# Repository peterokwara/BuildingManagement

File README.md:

# Table of Contents

- [Table of Contents](#table-of-contents)
- [Building Management System](#building-management-system)
- [Video example](#video-example)
- [Dashboard](#dashboard)
- [Hardware setup](#hardware-setup)
  - [Esp & Current sensor](#esp--current-sensor)
  - [Esp & Dht sensor](#esp--dht-sensor)
  - [Esp & Motion sensor](#esp--motion-sensor)
  - [Esp & Relay](#esp--relay)
- [Installation](#installation)
  - [Esp](#esp)
  - [Raspberry Pi](#raspberry-pi)
  - [Server](#server)
  - [Client](#client)
- [Usage](#usage)
  - [Raspberry Pi](#raspberry-pi-1)
  - [Website (server and client)](#website-server-and-client)
- [Contributing](#contributing)
- [License](#license)

# Building Management System

This project seeks to demonstrate the use of MQTT protocol and MERN stack for building an IoT Building Management System for commercial usage, where parameters such as building occupancy, energy demand, andenergy consumption are measured and displayed on an online database and dashboard.

A more detailed description of the project can be found [here](https://github.com/peterokwara/BuildingManagement/blob/master/Project%20Report.pdf).

# Video example

A video of the project working (hardware)

<a href="https://www.youtube.com/watch?v=Yh3uR8R79lM" target="_blank"></a>

A video of the project working (software)

<a href="https://youtu.be/3eJK0t_gp44
" target="_blank"></a>

# Dashboard

You can access the dashboard after you sign up [here](https://thawing-scrubland-94209.herokuapp.com/)

# Hardware setup

## Esp & Current sensor

Circuit design

Board design and the final look

## Esp & Dht sensor

Circuit design

Board design and the final look

## Esp & Motion sensor

Circuit design

Board design and the final look

## Esp & Relay

Circuit design

Board design and the final look

# Installation

## Esp

Installing in an ESP8266-01 and NodeMCU involves pushing the python files into the device whether it's via a usb to ttl or just a usb cable. This can be done using the command

```bash
sudo ampy --port /dev/ttyUSB0 --baud 115200 put main.py
sudo ampy --port /dev/ttyUSB0 --baud 115200 put config.py
sudo ampy --port /dev/ttyUSB0 --baud 115200 put connectWifi.py
```

You need to create a config.py file with the following information for each and every esp folder (current-sensor, dht-sensor, motion-sensor, relay-bulb, relay-fan)

```python
MQTT_CONFIG = {
    'SENSOR_ID': '',
    'MQTT_HOST': '',
    'PORT': '',
    'PUB_TOPIC': ''
}

WIFI_CONFIG = {
    'WIFI_ESSID': '',
    'WIFI_PASSWORD': ''
}
```

## Raspberry Pi

To install npm packages used for the Raspberry Pi, you run.

```bash
npm install axios mongoose mqtt
```

You also need to create a config folder and have two files that contain config/broker.js

```js
module.exports = {
  brokerUrl: ""
};
```

and config/server.js

```js
module.exports = {
  serverUrl: ""
};
```

## Server

To install npm packages used for the server, you run.

```bash
npm install axios bcryptjs body-parser concurrently cors express gravatar jsonwebtoken mongoose mqtt passport passport-jwt recharts validator
```

You also need to have a config/keys_dev.js with the configuration above. The mongoUri and secretOrKey are obtained when you create a mongodb on https://mlab.com the database I used.

```js
module.exports = {
  mongoUri: "",
  secretOrKey: ""
};
```

## Client

To install npm packages used for the client, you run.

```bash
npm install jwt-decode axios react-redux redux recharts redux-thunk semantic-ui-css semantic-ui-react
```

# Usage

## Raspberry Pi

To run the code for Raspberry Pi just cd into the folder and run

```bash
node app.js
```

To ensure that the Raspberry Pi runs the code whenever it boots, edit the rc.local file

```
sudo nano /etc/rc.local
```

and add

```
node app.js &
```

## Website (server and client)

To run a local development of the website, all you need to do is to do the installation setup then once that is done

```
cd site && npm run dev
```

# Contributing

Pull requests are welcome. For major changes, please open an issue first to discuss what you would like to change.

Please make sure to update tests as appropriate.

# License

[MIT](https://github.com/peterokwara/BuildingManagement/blob/master/LICENSE)

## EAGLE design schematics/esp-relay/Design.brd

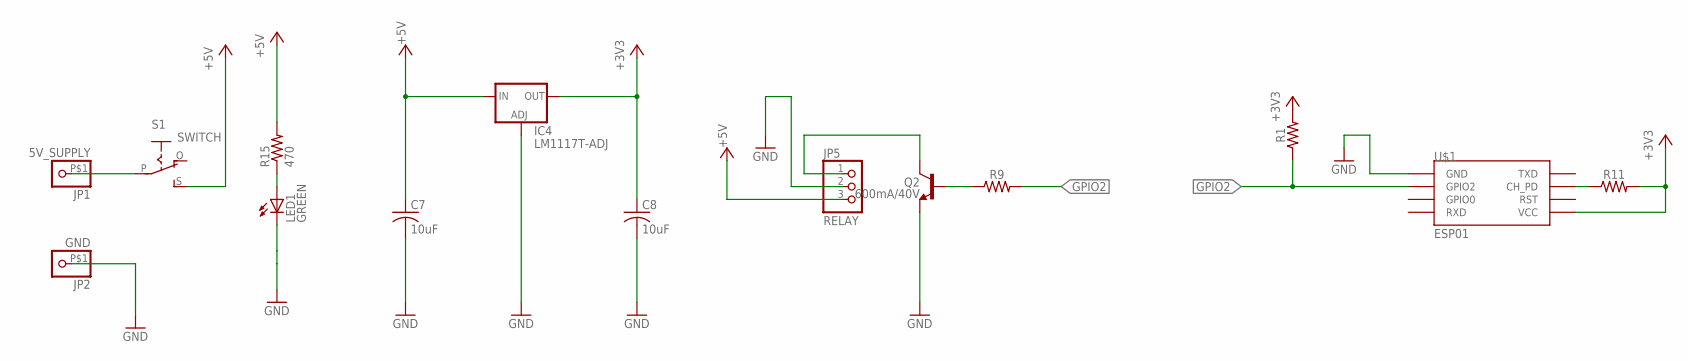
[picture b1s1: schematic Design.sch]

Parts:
C7, C8: 10uF; C025-025X050
IC4: LM1117T-ADJ; TO220
JP1: 5V_SUPPLY; 1X1-BIGPOGO
JP2: GND; 1X1-BIGPOGO
JP5: RELAY; 1X03
LED1: GREEN; LED5MM
Q2: 600mA/40V; TO-92
R1, R11: 10k; 0207/12
R9: 4.7k; 0207/12
R15: 470; 0207/12
S1: SWITCH; EG1218
U$1: ESP01

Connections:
+3V3: C8.1, IC4.2 (OUT), R1.2, R11.2, U$1.VCC
+5V: C7.1, IC4.3 (IN), JP5.3, R15.2, S1.S
GND: C7.2, C8.2, IC4.1 (ADJ), JP2.P$1, JP5.2, LED1.K (C), Q2.3 (E), U$1.GND
GPIO2: R1.1, R9.2, U$1.GPIO2
unnamed: JP1.P$1, S1.P
unnamed: R11.1, U$1.CH_PD
unnamed: JP5.1, Q2.1 (C)
unnamed: Q2.2 (B), R9.1
unnamed: LED1.A, R15.1

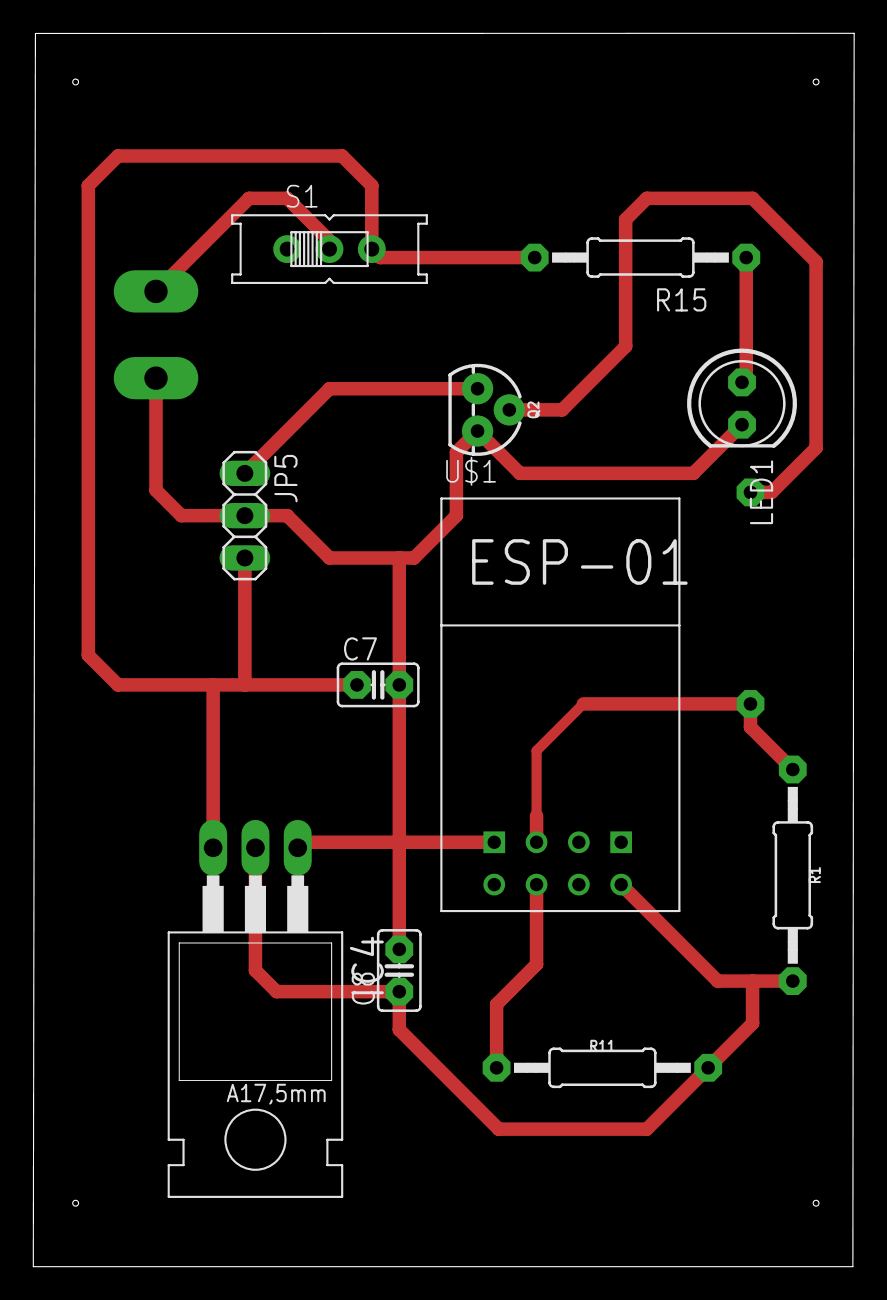
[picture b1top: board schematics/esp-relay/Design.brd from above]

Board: 2 copper layers, 49.3 x 74.0 mm, 14 parts (1 on the bottom side), 9 nets.

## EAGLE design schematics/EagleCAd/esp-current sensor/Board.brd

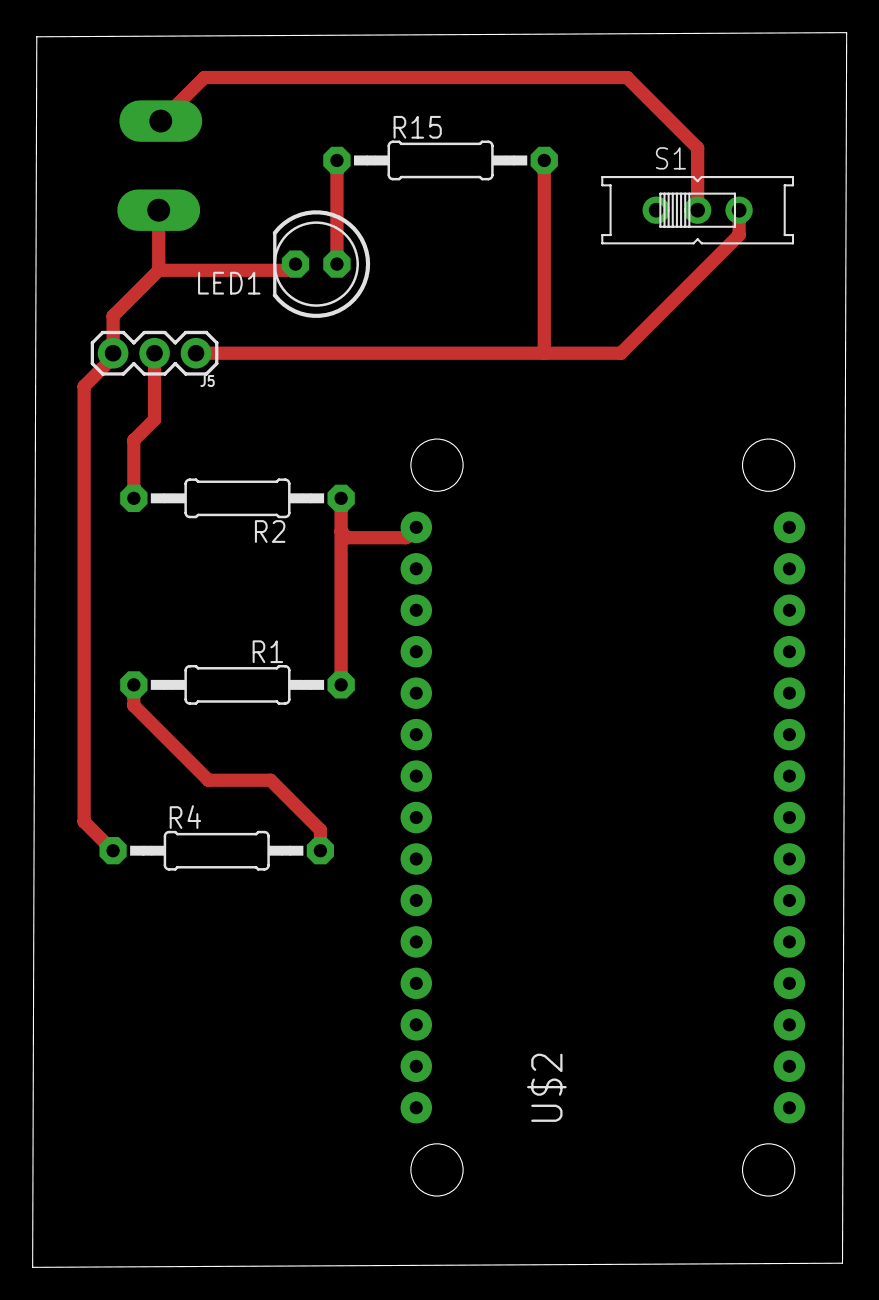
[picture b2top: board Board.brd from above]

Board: 2 copper layers, 49.9 x 75.6 mm, 10 parts (0 on the bottom side), 7 nets.

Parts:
J5: 1x3 RA Female .1"; 1X03
JP1: 5V_SUPPLY; 1X1-BIGPOGO
JP2: GND; 1X1-BIGPOGO
LED1: GREEN; LED5MM
R1: 101; 0207/12
R2: 10k; 0207/12
R4: 2.4k; 0207/12
R15: 470; 0207/12
S1: SWITCH; EG1218
U$2: ESP12E_DEVKIT

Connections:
+5V: J5.1, R15.2, S1.S
ADO: R1.2, R2.1, U$2.AD0
GND: J5.3, JP2.P$1, LED1.K, R4.1, U$2.GND@0
unnamed: R1.1, R4.2
unnamed: JP1.P$1, S1.P
unnamed: LED1.A, R15.1
V0: J5.2, R2.2

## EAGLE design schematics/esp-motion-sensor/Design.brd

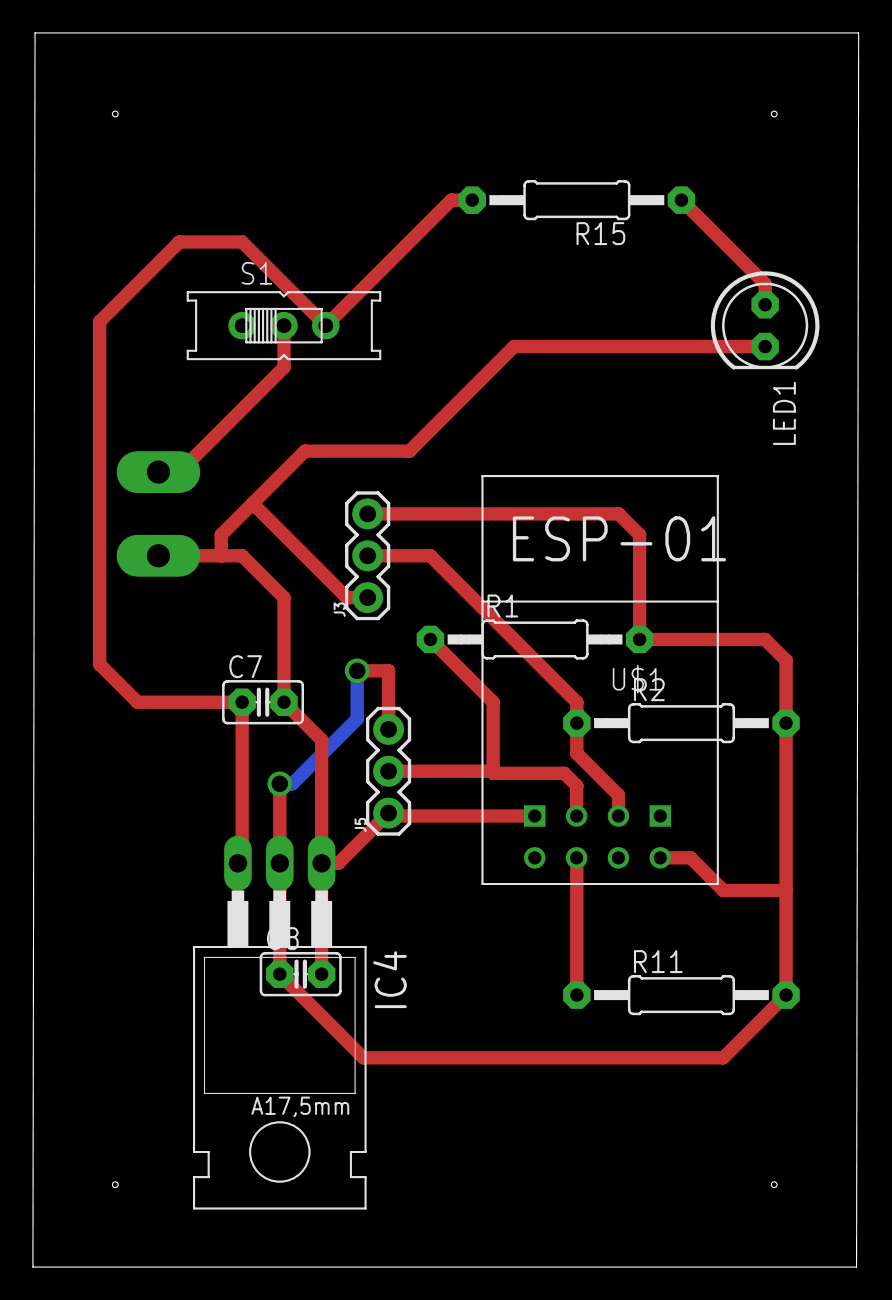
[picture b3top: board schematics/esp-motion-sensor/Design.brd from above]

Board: 2 copper layers, 50.1 x 74.9 mm, 14 parts (0 on the bottom side), 8 nets.

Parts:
C7, C8: 10uF; C025-025X050
IC4: LM1117T-ADJ; TO220
J3, J5: 1x3 RA Female .1"; 1X03
JP1: 5V_SUPPLY; 1X1-BIGPOGO
JP2: GND; 1X1-BIGPOGO
LED1: GREEN; LED5MM
R1, R2, R11: 10k; 0207/12
R15: 470; 0207/12
S1: SWITCH; EG1218
U$1: ESP01

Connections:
+3V3: C8.1, IC4.2, J3.3, J5.3, R1.2, R2.2, R11.2, U$1.VCC
+5V: C7.1, IC4.3, R15.2, S1.S
GND: C7.2, C8.2, IC4.1, J3.1, J5.1, JP2.P$1, LED1.K, U$1.GND
GPIO0: J3.2, R2.1, U$1.GPIO0
GPIO2: J5.2, R1.1, U$1.GPIO2
unnamed: JP1.P$1, S1.P
unnamed: R11.1, U$1.CH_PD
unnamed: LED1.A, R15.1

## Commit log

2019-01-18 Remove boilerplate
2019-01-18 Add sign up page
2019-01-18 Add login page
2019-01-25 Add code for server side authentication
2019-01-25 Add routes and authentication
2019-01-25 Add feathers js, react router and semantic ui
2019-01-25 Add js for feathers js communication with backend
2019-01-25 Add browserrouter for routing operations
2019-01-25 Add layout for left side menu
2019-01-25 Add code for layout for the top menu
2019-01-25 Add login page and login logic
2019-01-25 Add signup page and signup logic
2019-01-25 Add dashboard to contain topnav and leftnav
2019-01-25 Test code for the server
2019-01-25 Ignore the lock file
2019-01-25 Add lock file to gitignore
2019-01-27 Add code to connect to wifi
2019-01-27 Add code to connect to wifi and read from gpio pin
2019-01-28 Chang setup to use python config
2019-01-30 Pir sensor 1 sending data to raspi
2019-01-30 Update two code to work for both pir sensors
2019-02-01 Add schematics for the PIR motion sensor and esp
2019-02-04 Add package file for site
2019-02-04 Ignore files
2019-02-05 Add a procfile
2019-02-05 Remove client and server install
2019-02-05 Add postbuild instructions
2019-02-05 Remove build instructions
2019-02-05 Change port that create-react-app binds to
2019-02-05 Change default port to 8080
2019-02-05 Run client first then client next
2019-02-05 Change postbuild to build client then server
2019-02-05 Remove publish public
2019-02-06 Remove feathers js files
2019-02-06 Add new package.json files for the backend
2019-02-06 Create a basic web server using express
2019-02-06 Connect to remote mongodb database
2019-02-06 Add a users route
2019-02-06 Add body parser
2019-02-06 Add model for the user data to be stored
2019-02-06 Store user data posted
2019-02-06 Add user avatar
2019-02-06 Add library for user avatar and encrypt password
2019-02-06 Print message whether user authenticated successfully or not
2019-02-06 Create jwt token
2019-02-06 Add jwt authentication strategy
2019-02-07 Add user validation
2019-02-07 Change port backend runs on
2019-02-07 Include script for running frontend and backend concurrently
2019-02-07 Remove run on port 8080
2019-02-07 Add new files to ignore
2019-02-08 Remove create react app components
2019-02-08 Setup sign up form
2019-02-08 Create sign in form
2019-02-08 Add files to ignore
2019-02-08 Set up paths for sign in and sign up page
2019-02-08 Set up route to sign up page
2019-02-08 Handle onSubmit
2019-02-09 Set up redux
2019-02-09 Add redux, axios and proxy
2019-02-09 Use cors
2019-02-09 Add cors to the file
2019-02-09 Add redux to app
2019-02-09 Get the user flow
2019-02-09 Show errors in the redux dev tools
2019-02-09 Change proxy value to correct value
2019-02-09 Go to login after successful registration
2019-02-09 Show error when fields are not filed well
2019-02-09 Fix proptype error
2019-02-09 Set up login for the user
2019-02-09 Change rendering for errors.email error
2019-02-09 Add decode for the token module
2019-02-09 Go to sign in after sign up
2019-02-09 Go to main page after sign up
2019-02-09 Create a top menu
2019-02-09 Add actions for logging out
2019-02-09 Complete redirect to logout
2019-02-09 Starter code
2019-02-09 Rough instructions
2019-02-10 Ignore config files
2019-02-10 Connect to mongodb and mqtt broker and listen to topics
2019-02-10 Add package file
2019-02-10 Ignore lock file
2019-02-10 Create route for saving pir sensor data
2019-02-10 Add code for sending pir motion sensor data
2019-02-10 Change publish data from pir sensor
2019-02-10 Create the left menu
2019-02-10 Add left menu to mainpage
2019-02-10 Add basic layout
2019-02-10 Create table for motion sensor data
2019-02-10 Change from pir to motionsensors
2019-02-10 Fix route problems
2019-02-10 Fix logout bug when jwt token expires
2019-02-10 Fix error in comments
2019-02-10 Add route to get all motion sensor data
2019-02-10 Add devices reducer
2019-02-16 Add schematic files from fritzing software
2019-02-16 Upload better breadboard schematic
2019-02-16 Upload changes to bread board schematic
2019-02-18 Add routing for the new paths
2019-02-19 Add simple code to get temperature data from dht11
2019-02-19 Add config file to gitignore
2019-02-19 Send humidity and temperature data to raspberry pi
2019-02-20 Change file name and publish method
2019-02-20 Remove former temperature files
2019-02-20 Add updated version of mongoose, and new app.js file to run in the cloud
2019-02-20 Add file for saving data to database
2019-02-20 Send both temperature and humidity data
2019-02-20 Add route for dhtsensor
2019-02-20 Create schema for dhtsensor
2019-02-20 Create routes for the dht sensor
2019-02-20 Change location of export
2019-02-20 Add code to send climate data to server to be stored
2019-02-20 Add code to fetch temperature data and render it on a table
2019-02-20 Remove temperature components
2019-02-21 Add line chart component to display temperature and humidity values
2019-02-21 Add recharts for rendering charts
2019-02-23 Add raspberry pi photo
2019-02-23 Remove raspi code
2019-02-23 Ignore config file
2019-03-21 Remove sub-topic
2019-04-18 Add etching files for all circuits
2019-04-24 Add eagle file and fritzing file separately
2019-04-25 Add field for access level, for user
2019-04-25 Add route for getting all users
2019-04-25 Change name from dhtsensor to climate
2019-04-25 Create and list rooms
2019-04-25 Change from motionsensors to occupancy
2019-04-25 Allow date to be populated automatically
2019-04-25 Enable storage and retrieval of power consumption data
2019-04-25 Change dhtsensor to climate
2019-04-25 Enable one to store and fetch data on devices
2019-04-25 Change results that are sent back
2019-04-25 Change url of data sent fom dhtsensor to climate
2019-04-25 Add power component and fetch data power
2019-04-25 Change line chart component to accept props instead of hard coded values
2019-04-25 Add props that are sent to the dht sensor component
2019-04-25 Show data on devices state
2019-04-26 Add code to show/display room occupancy
2019-04-26 Rename from dhtsensor to climate
2019-04-26 Add dashboard showing all the current information
2019-04-26 Modify left menu contents
2019-04-26 Remove unnecessary data
2019-04-26 Remove semantic ui components not in use
2019-04-26 Add legend
2019-04-26 Add relevant legend title for x_axis and y_axis
2019-04-26 Remove stuff for react devtools to avoid it showing it showing a blank page
2019-04-26 Remove access control field
2019-04-26 Add key configuration files
2019-04-26 Add keys_dev to gitignore
2019-04-26 Prepare for heroku deploy
2019-04-26 Remove unwanted components
2019-04-26 Change prefix error
2019-04-26 Add variable for env port
2019-04-27 Ignore node modules file and config file
2019-04-27 Ignore package-lock.json file
2019-04-27 Add code for the raspberry pi node js file
2019-04-27 Add package.json file
2019-04-29 Send data with one pir motion sensor
2019-04-30 New code for the motion sensors
2019-05-04 Tun on fan if temperature is above 30 degrees and turn off fan if temperature is below
2019-05-05 Use interrupts to capture motion
2019-05-05 Add measure and delay missing from code
2019-05-08 Add comments to code
2019-05-08 Add comments
2019-05-09 Add project report
2019-05-19 Add asset for readme
2019-05-19 Remove test file
2019-05-19 Change heading indentation
2019-05-19 Add more assets for Readme
2019-05-19 Fix typo
2019-05-19 Create License
2019-05-19 Add link to license
2019-05-19 Add content on dashboard
2019-05-19 Add asset file for the dashboard

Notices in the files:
parts and their libraries:
SparkFun-Connectors: Licensing: Creative Commons ShareAlike 4.0 International - https://creativecommons.org/licenses/by-sa/4.0
